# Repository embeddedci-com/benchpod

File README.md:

# BenchPod

**NOTE1: Some tagged versions will have obvious mistakes in them, but as those got built, they're in the repo for historical reasons.**

**NOTE2: Don't build these boards yourself without any necessary changes. The current tagged versions are not production-ready yet.**

**An open hardware bench tool with sensor sim, CAN, analog I/O, and power control, with a Python SDK and pytest integration.**

Embedded teams often end up with a bench full of equipment that's hard to share, hard to automate, and difficult to use remotely. Setting up tests often means being physically present, and that doesn't scale well across a team.

BenchPod is an attempt to make that easier. One board with sensor simulation over I2C and SPI, CAN bus, analog input and output, programmable power control, a logic analyzer, and an FPGA for fast protocol mocking, connected over WiFi so it can be shared across a team or accessed remotely. A Python SDK and pytest integration make it straightforward to go from manual bench work to automated tests without changing your setup.

This repo contains the KiCad source files for the board, plus the SPICE simulations used while designing the analog front ends.

---

## What's in this repo

```
pcb/
  benchpod/                      # KiCad project for the analog + digital board
    vbench-pod.kicad_pro         #   KiCad project file
    vbench-pod.kicad_pcb         #   PCB layout
    vbench-pod.kicad_sch         #   Top-level schematic
    analog-power-v2.kicad_sch    #   Analog supply rails
    analog-switching.kicad_sch   #   Analog signal routing / muxing
    analog-to-digital-v2.kicad_sch  # ADC front end
    digital-to-analog-v2.kicad_sch  # DAC output stage
    LogicAnalyzer.kicad_sch      #   Logic analyzer
    power.kicad_sch              #   Power control
    ethernet.kicad_sch           #   Ethernet
    usb.kicad_sch                #   USB
    fp-lib-table                 #   Footprint library references
    sym-lib-table                #   Symbol library references
  benchpod-digital/              # KiCad project for the digital-only board (same sheet layout)
  libs/                          # Shared symbol, footprint, and 3D-model libraries

spice/                           # LTspice / ngspice simulations for the analog front ends
  adc-v1/  adc-v2/  dac-v2/
```

Library paths in `fp-lib-table`, `sym-lib-table`, and the PCB are stored relative to
the project (`${KIPRJMOD}/..`), so the project opens in KiCad straight after cloning.

---

## Which board do I have?

The board name is printed on the silkscreen (for example "BenchPod v3-r1"). Find it in the table
below to get the git tag with the exact design files for your board:

| Silkscreen | Board | Tag | KiCad project | What changed |
|---|---|---|---|---|
| BenchPod v3 | Analog + digital | `analog-v3` | `pcb/benchpod` | First v3 board. STM32H563ZIT6, INA238 current monitors. |
| BenchPod v3-Digital | Digital only | `digital-v3` | `pcb/benchpod-digital` | First digital-only board: the v3 without the analog section. STM32H563ZGT6 (1 MB flash), INA226 current monitors. |
| BenchPod v3-r1 | Analog + digital | `analog-v3r1` | `pcb/benchpod` | STM32H563ZGT6 and INA226 like the digital board. Monitors the pod's own current (INA226 at 0x41). The 5.5 V analog rail comes from a 7 V boost instead of the 14 V rail, so U50 no longer runs hot. TPS65131 compensation caps fixed. THS4551 and TPS7A2050 in their smaller packages (RUN, DQN). |
| BenchPod v3r2-Digital | Digital only | `digital-v3r2` | `pcb/benchpod-digital` | Monitors the pod's own current (INA226 at 0x41). |
| BenchPod v3-r2 | Analog + digital | `analog-v3r2` | `pcb/benchpod` | One DAC8554 quad DAC (a channel per output) replaces the DAC8551 and its two TMUX1104 muxes. The ±14 V supply starts off and the firmware switches it on. 0.1 % resistors around the ADC driver for a smaller zero offset between pods. Fixed 9.1 pF ADC compensation instead of the trimmer. SWD and USART2 on DNP 2x2 headers instead of H1-H3. More ESD clamps (USB CC, +1V8, LA_VCCIO, the 0-5 V SMA). Board revision strap 2.70 V. |
| BenchPod v3r3-Digital | Digital only | `digital-v3r3` | `pcb/benchpod-digital` | 24-pin FFC connector (CN1) for the analog module. The module 5 V and the USB-A bridge 5 V are switched by SY6280AAC power switches, with TVS diodes on the 5 V outputs. 3.3 V buck becomes a TPS62130A with a 2.2 uH inductor. PSRAM in SOP-8. Ethernet EMI changes from the Microchip and TI reference designs: RJ45 chassis ground straight to GND, center taps fed through a 0 ohm resistor, 8.2 pF on the four data lines, a flow-through TPD4E05U06 ESD clamp. 100 nF + 470 pF at the J4, J5 and J6 terminals. Connectors placed for the enclosure. |
| BenchPod v3-r3-analog | Analog module | `analog-v3r3` | `pcb/benchpod-analog` | First analog module: the analog section on its own board, connected to the v3r3 digital board by a 24-pin FFC (CN1). Front-panel connectors for the enclosure: a lead-free BNC for the ADC input (ready for 10x probes), pluggable terminal blocks for the DAC outputs (one 6-pin block) and the 4-20 mA loop. Module ID EEPROM. +3V3 from an AP2112K-3.3. |
| BenchPod v3-r4-analog | Analog module | `analog-v3r4` | `pcb/benchpod-analog` | ADC low range: relay K5 switches the input divider from ±32.8 V to ±5.46 V for 6x the resolution. |
| BenchPod v4-Digital | Digital only | not tagged yet (on `main`) | `pcb/benchpod-digital` | First board with built-in 5 V I/O: an LSF0108 level shifter on every LA channel, 1.8, 3.3 or 5 V, J1 pin 21 as the switched and measured reference. Pull-up or pull-down with 10k, 2.2k or both on every channel (two TCA6416A). Switched DUT supplies on J1: pin 17 3.3 V behind a current-limited switch (SY6280AAC, about 1.45 A), pin 18 1.8 V from its own regulator (AP2112K-1.8). USB-A host port for the DUT's own USB (flashing and USB host). Second board revision strap. Memory-mapped W25Q. Not built yet. |
| BenchPod v4-Analog | Analog module | not tagged yet (on `main`) | `pcb/benchpod-analog` | 4-20 mA input behind a 30 mA limiter with a 100 ohm sense resistor. DAC clock and data swapped on the flat cable (pairs with the v4 digital board). More ESD clamps. Module EEPROM revision 4.0. Not built yet. |

To get the files for your board, check out its tag:

```
git checkout analog-v3r1
```

Every tag holds all KiCad projects; use the folder from the table. Older boards: `v1.0.0` and
`v1.0.1` are v1, `v2.0.0` is v2.

The v3 tags used to be named `v3.0.0` (now `analog-v3`), `v3.0.1-digital` (now `digital-v3`),
`v3.0.1-analog` (now `analog-v3r1`) and `v3.0.2-digital` (now `digital-v3r2`).

v4 is the first board with 5 V I/O. It was called digital v3r4 and analog module v3r5 while it
was designed; the feature jump made it a major version. A v4 digital board needs a v4 analog
module (or both older): the DAC lines on the flat cable are swapped.

One firmware runs on all v3 and v4 boards. The pod's own current needs firmware newer than 3.5.1.
The v3-r2 board needs firmware newer than 3.9.4: older firmware runs it as a v3-r1 and its DAC
outputs and ±12 V stay off.

---

## License

Hardware (schematics, PCB layout) is released under [CERN OHL-W v2](https://ohwr.org/cern_ohl_w_v2.txt).

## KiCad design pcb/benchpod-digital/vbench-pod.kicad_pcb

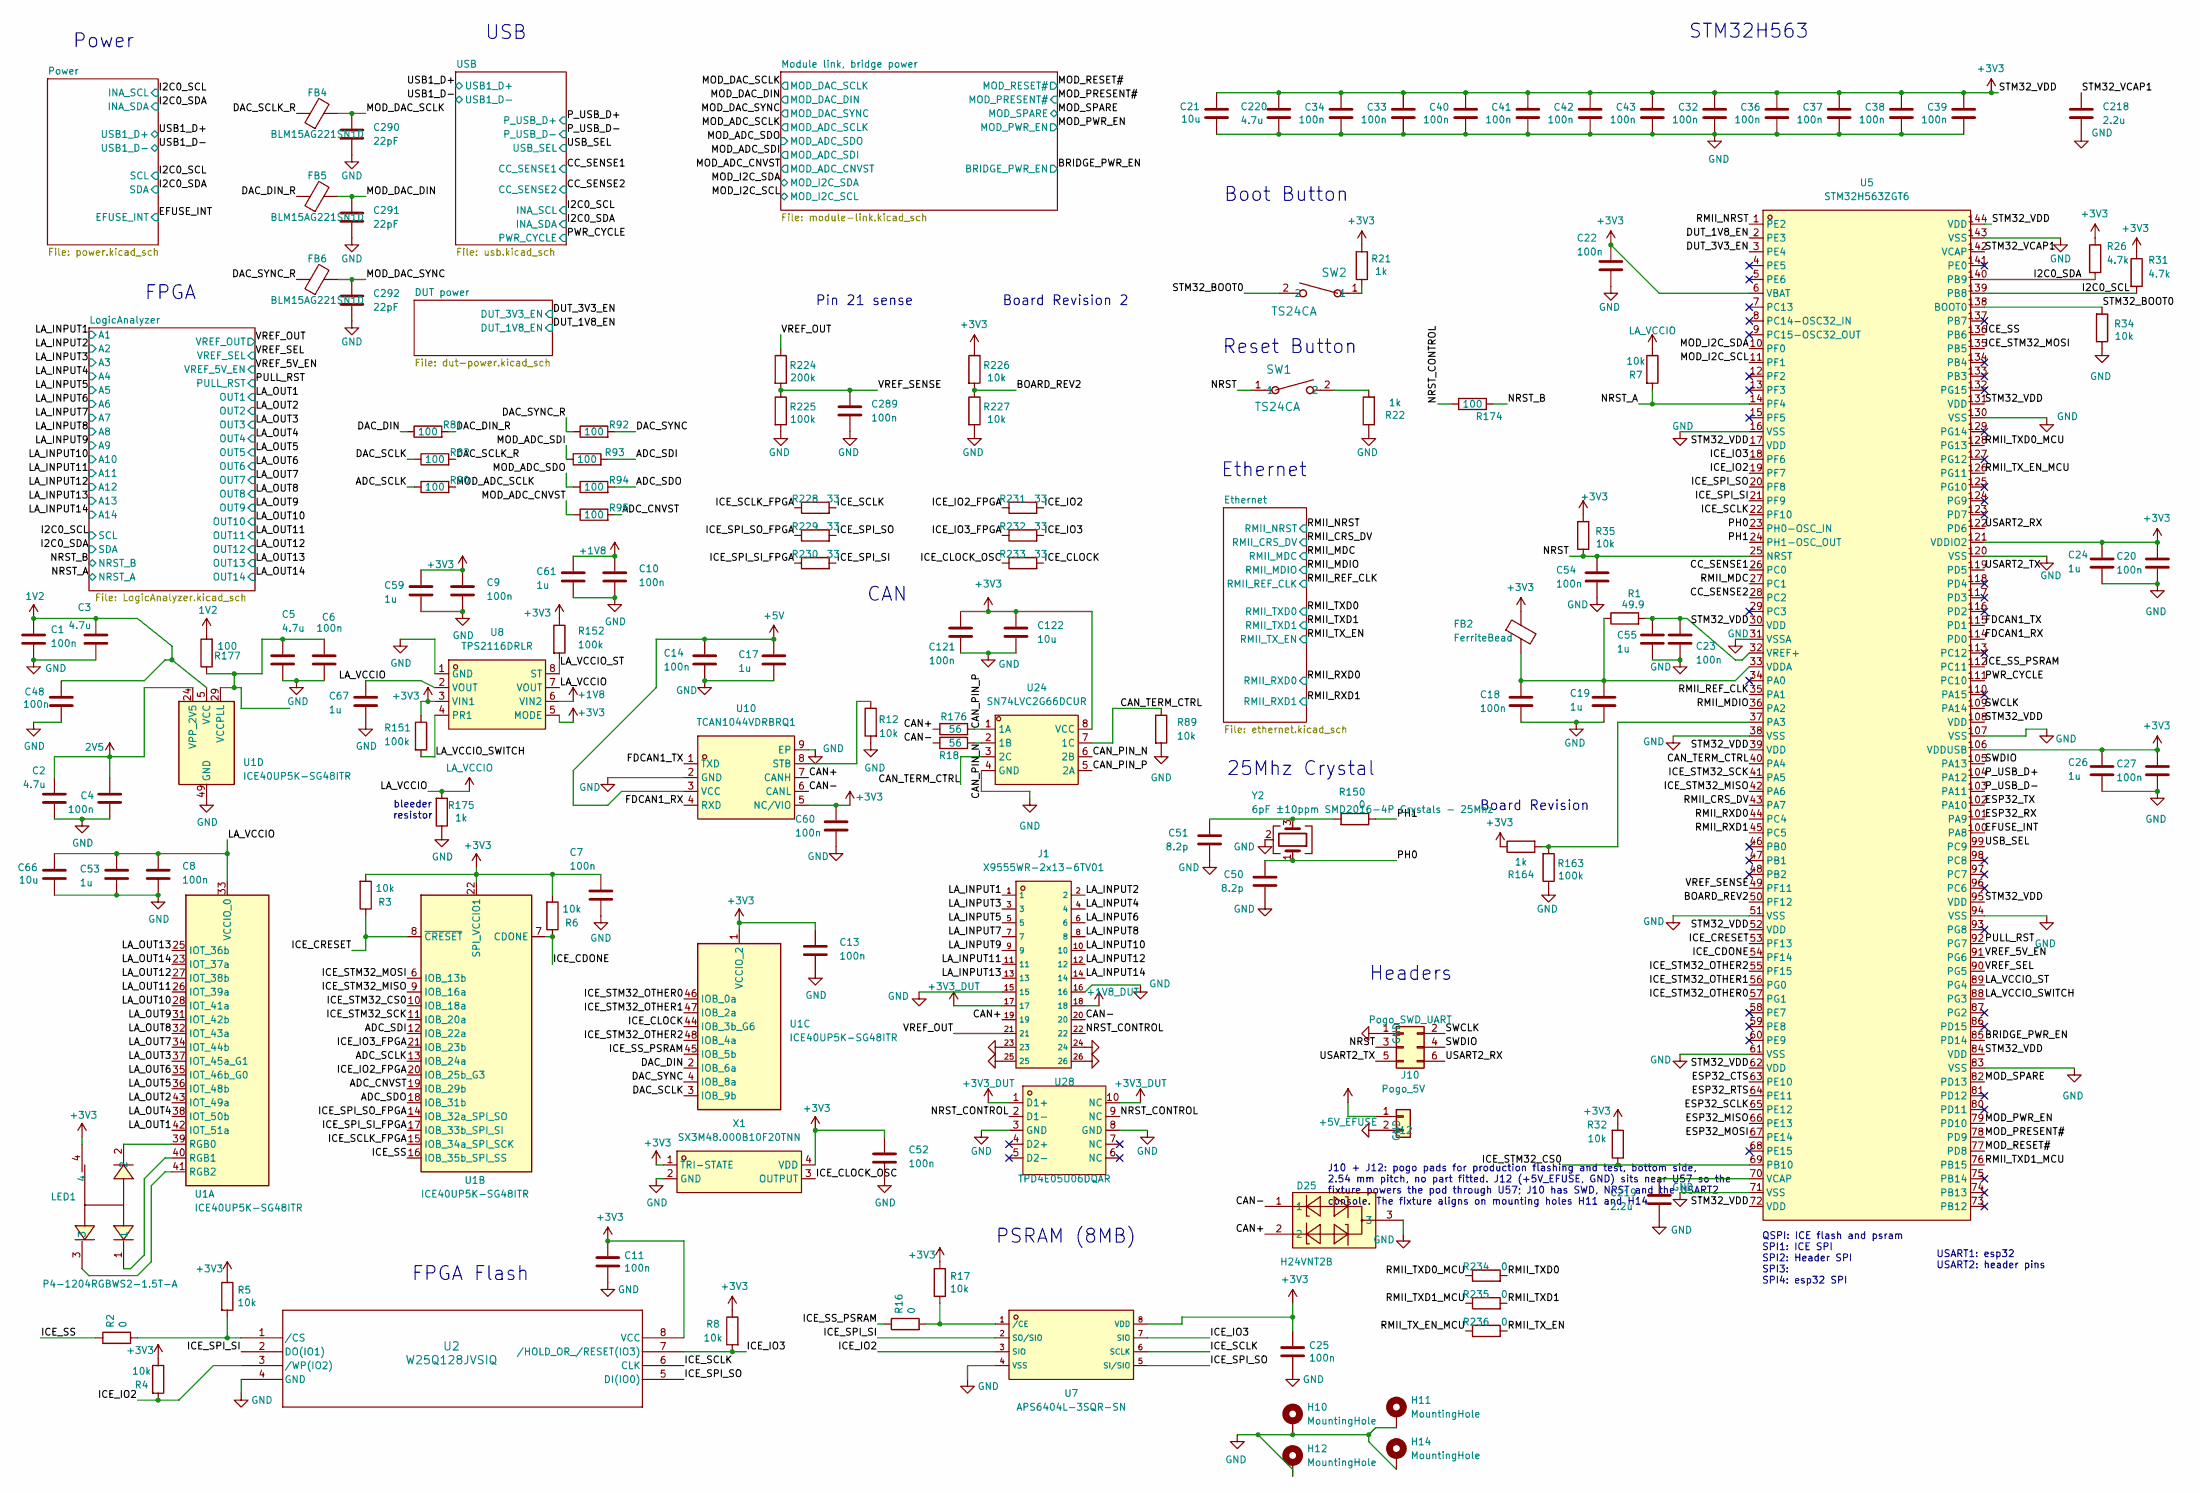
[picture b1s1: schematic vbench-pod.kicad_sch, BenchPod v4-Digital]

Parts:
C1, C4, C6, C7, C8, C9, C10, C13, C14, C18, C20, C22, C23, C27, C48, C52, C54, C60: 100n; C_0402_1005Metric; MPN CC0603KRX7R9BB104; LCSC C307331
C2, C3, C5, C220: 4.7u; C_0805_2012Metric; LCSC C98192
C11, C25, C32, C33, C34, C36, C37, C38, C39, C40, C41, C42, C43, C121, C289: 100n; C_0402_1005Metric; LCSC C307331
C17, C24, C26, C53, C59, C67: 1u; C_0402_1005Metric; MPN CL05A105KA5NQNC; LCSC C52923
C19, C55, C61: 1u; C_0402_1005Metric; MPN GRM155R61H105KE05D; LCSC C1518208
C21, C66, C122: 10u; C_0603_1608Metric; LCSC C96446
C50, C51: 8.2p; C_0402_1005Metric; LCSC C1579
C218, C219: 2.2u; C_0603_1608Metric; LCSC C415535
C290, C291, C292: 22pF; C_0402_1005Metric; MPN 0402CG220J500NT; LCSC C1555
D25: H24VNT2B; SOT-23; MPN H24VNT2B; LCSC Part C20615827
FB2: FerriteBead; C85833_L0603; LCSC C85833
FB4, FB5, FB6: BLM15AG221SN1D; L_0402_1005Metric; MPN BLM15AG221SN1D; LCSC C85813
H10, H11, H12, H14: MountingHole; MountingHole_2.7mm_M2.5_Pad_Via
J1: X9555WR-2x13-6TV01; C2682221_CONN-TH_X9555WR-2X13-6TV01; LCSC C2682221
J10: Pogo_SWD_UART; Pogo_Pads_2x03_P2.54mm
J12: Pogo_5V; Pogo_Pads_1x02_P2.54mm
LED1: P4-1204RGBWS2-1.5T-A; C2827295_LED-SMD_4P-L3.2-W1.5_P4-1204RGBWS2-1.5T-A; MPN P4-1204RGBWS2-1.5T-A; LCSC Part C2827295
R1: 49.9; R_0402_1005Metric; LCSC C325388
R2, R16, R150, R234, R235, R236: 0; R_0402_1005Metric; LCSC C17168
R3, R4, R6, R7, R8, R12, R32, R34, R35, R89, R226, R227: 10k; R_0402_1005Metric; LCSC C25744
R5, R17: 10k; R_0402_1005Metric; JLC_DNF true
R18, R176: 56; R_0402_1005Metric; LCSC C3013179
R21, R22, R164, R175: 1k; R_0402_1005Metric; LCSC C11702
R26, R31: 4.7k; R_0402_1005Metric; LCSC C25900
R81, R82, R90, R92, R93, R94, R95, R177: 100; R_0402_1005Metric; LCSC C25076
R151, R152, R163, R225: 100k; R_0402_1005Metric; LCSC C25741
R174: 100; R_0603_1608Metric; Manufacturer_Part_Number PS03W4F1000T5E; LCSC C2784878
R224: 200k; R_0402_1005Metric; LCSC C25764
R228, R229, R230, R231, R232, R233: 33; R_0402_1005Metric; LCSC C25105
SW1, SW2: TS24CA; C393942_SW-SMD_2P-TS24CA; LCSC C393942
U1: ICE40UP5K-SG48ITR; QFN-48_L7.0-W7.0-P0.50-TL-EP5.4-1; LCSC C2678152
U2: W25Q128JVSIQ; SOIC-8_L5.3-W5.3-P1.27-LS8.0-BL; MPN W25Q128JVSIQ; LCSC C97521
U5: STM32H563ZGT6; LQFP-144_L20.0-W20.0-P0.50-LS22.0-TL; LCSC Part C29271104
U7: APS6404L-3SQR-SN; C5333729_SOIC-8_L4.9-W3.9-P1.27-LS6.0-BL; LCSC C5333729
U8: TPS2116DRLR; SOT-583-8_L2.1-W1.6-P0.50-LS1.6-BL; MPN TPS2116DRLR; LCSC Part C3235557
U10: TCAN1044VDRBRQ1; VSON-8_L3.0-W3.0-P0.65-BR-EP; MPN TCAN1044VDRBRQ1; LCSC Part C5215851
U24: SN74LVC2G66DCUR; VSSOP-8_L2.1-W2.4-P0.50-LS3.2-BR; MPN SN74LVC2G66DCUR; LCSC Part C181970
U28: TPD4E05U06DQAR; C138714_USON-10_L2.5-W1.0-P0.50-BL; LCSC C138714
X1: SX3M48.000B10F20TNN; OSC-SMD_4P-L3.2-W2.5-BL; MPN SX3M48.000B10F20TNN; LCSC Part C5452690
Y2: 6pF ±10ppm SMD2016-4P Crystals - 25Mhz; Crystal_SMD_2016-4Pin_2.0x1.6mm; LCSC C49867546

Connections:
1V2: C1.2, C3.1, C48.2, R177.2, U1.5 (VCC), U1.30 (VCC); also elsewhere on the board
2V5: C2.1, C4.2, U1.24 (VPP_2V5); also elsewhere on the board
+1V8: C10.2, C61.2, U8.6 (VIN2); also elsewhere on the board
+3V3: C7.2, C9.2, C11.1, C13.2, C20.2, C21.1, C22.2, C24.2, C25.1, C26.2, C27.2, C32.1, C33.1, C34.1, C36.1, C37.1, C38.1, C39.1, C40.1, C41.1, C42.1, C43.1, C52.2, C59.2, C60.2, C121.1, C122.2, C220.1, FB2.1, LED1.4, R3.2, R4.1, R5.1, R6.2, R8.1, R17.1, R21.2, R26.1, R31.1, R32.2, R35.2, R151.1, R152.1, R164.1, R226.1, U1.1 (VCCIO_2), U1.22 (SPI_VCCIO1), U2.8 (VCC), U5.6 (VBAT), U5.17 (VDD), U5.30 (VDD), U5.39 (VDD), U5.52 (VDD), U5.62 (VDD), U5.72 (VDD), U5.84 (VDD), U5.95 (VDD), U5.106 (VDDUSB), U5.108 (VDD), U5.121 (VDDIO2), U5.131 (VDD), U5.144 (VDD), U7.8 (VDD), U8.3 (VIN1), U8.5 (MODE), U10.5 (NC/VIO), U24.8 (VCC), X1.1 (TRI-STATE), X1.4 (VDD); also elsewhere on the board
+5V: C14.2, C17.2, U10.3 (VCC); also elsewhere on the board
+5V_EFUSE: J12.1; also elsewhere on the board
/ADC_CNVST: R95.2, U1.19 (IOB_29b)
/ADC_SCLK: R90.1, U1.13 (IOB_24a)
/ADC_SDI: R93.2, U1.12 (IOB_22a)
/ADC_SDO: R94.2, U1.18 (IOB_31b)
/BOARD_REV2: R226.2, R227.1, U5.50 (PF12)
/BRIDGE_PWR_EN: U5.85 (PD14); also elsewhere on the board
/CAN+: D25.2, J1.19, R176.1, U10.7 (CANH)
/CAN-: D25.1, J1.20, R18.1, U10.6 (CANL)
/CAN_PIN_N: R18.2, U24.2 (1B), U24.6 (2B)
/CAN_PIN_P: R176.2, U24.1 (1A), U24.5 (2A)
/CAN_TERM_CTRL: R89.1, U5.40 (PA4), U24.3 (2C), U24.7 (1C)
/CC_SENSE1: U5.26 (PC0); also elsewhere on the board
/CC_SENSE2: U5.28 (PC2); also elsewhere on the board
/DAC_DIN: R81.1, U1.2 (IOB_6a)
/DAC_DIN_R: FB5.1, R81.2
/DAC_SCLK: R82.1, U1.3 (IOB_9b)
/DAC_SCLK_R: FB4.1, R82.2
/DAC_SYNC: R92.2, U1.4 (IOB_8a)
/DAC_SYNC_R: FB6.1, R92.1
/DUT_1V8_EN: U5.2 (PE3); also elsewhere on the board
/DUT_3V3_EN: U5.3 (PE4); also elsewhere on the board
/EFUSE_INT: U5.100 (PA8); also elsewhere on the board
/ESP32_CTS: U5.63 (PE10)
/ESP32_MISO: U5.66 (PE13)
/ESP32_MOSI: U5.67 (PE14)
/ESP32_RTS: U5.64 (PE11)
/ESP32_RX: U5.101 (PA9)
/ESP32_SCLK: U5.65 (PE12)
/ESP32_TX: U5.102 (PA10)
/FDCAN1_RX: U5.114 (PD0), U10.4 (RXD)
/FDCAN1_TX: U5.115 (PD1), U10.1 (TXD)
/I2C0_SCL: R31.2, U5.139 (PB8); also elsewhere on the board
/I2C0_SDA: R26.2, U5.140 (PB9); also elsewhere on the board
/ICE_CDONE: R6.1, U1.7 (CDONE), U5.54 (PF14)
/ICE_CLOCK: R233.2, U1.44 (IOB_3b_G6)
/ICE_CLOCK_OSC: R233.1, X1.3 (OUTPUT)
/ICE_CRESET: R3.1, U1.8 (~CRESET), U5.53 (PF13)
/ICE_IO2: R4.2, R231.2, U2.3 (/WP(IO2)), U5.19 (PF7), U7.3 (SIO)
/ICE_IO2_FPGA: R231.1, U1.20 (IOB_25b_G3)
/ICE_IO3: R8.2, R232.2, U2.7 (/HOLD_OR_/RESET(IO3)), U5.18 (PF6), U7.7 (SIO)
/ICE_IO3_FPGA: R232.1, U1.21 (IOB_23b)
/ICE_SCLK: R228.2, U2.6 (CLK), U5.22 (PF10), U7.6 (SCLK)
/ICE_SCLK_FPGA: R228.1, U1.15 (IOB_34a_SPI_SCK)
/ICE_SPI_SI: R230.2, U2.2 (DO(IO1)), U5.21 (PF9), U7.2 (SO/SIO)
/ICE_SPI_SI_FPGA: R230.1, U1.17 (IOB_33b_SPI_SI)
/ICE_SPI_SO: R229.2, U2.5 (DI(IO0)), U5.20 (PF8), U7.5 (SI/SIO)
/ICE_SPI_SO_FPGA: R229.1, U1.14 (IOB_32a_SPI_SO)
/ICE_SS: R2.1, U1.16 (IOB_35b_SPI_SS), U5.136 (PB6)
/ICE_SS_PSRAM: R16.1, U1.45 (IOB_5b), U5.112 (PC11)
/ICE_STM32_CS0: R32.1, U1.10 (IOB_18a), U5.69 (PB10)
/ICE_STM32_MISO: U1.9 (IOB_16a), U5.42 (PA6)
/ICE_STM32_MOSI: U1.6 (IOB_13b), U5.135 (PB5)
/ICE_STM32_OTHER0: U1.46 (IOB_0a), U5.57 (PG1)
/ICE_STM32_OTHER1: U1.47 (IOB_2a), U5.56 (PG0)
/ICE_STM32_OTHER2: U1.48 (IOB_4a), U5.55 (PF15)
/ICE_STM32_SCK: U1.11 (IOB_20a), U5.41 (PA5)
/LA_INPUT1: J1.1; also elsewhere on the board
/LA_INPUT2: J1.2; also elsewhere on the board
/LA_INPUT3: J1.3; also elsewhere on the board
/LA_INPUT4: J1.4; also elsewhere on the board
/LA_INPUT5: J1.5; also elsewhere on the board
/LA_INPUT6: J1.6; also elsewhere on the board
/LA_INPUT7: J1.7; also elsewhere on the board
/LA_INPUT8: J1.8; also elsewhere on the board
/LA_INPUT9: J1.9; also elsewhere on the board
/LA_INPUT10: J1.10; also elsewhere on the board
/LA_INPUT11: J1.11; also elsewhere on the board
/LA_INPUT12: J1.12; also elsewhere on the board
/LA_INPUT13: J1.13; also elsewhere on the board
/LA_INPUT14: J1.14; also elsewhere on the board
/LA_OUT1: U1.42 (IOT_51a); also elsewhere on the board
/LA_OUT2: U1.43 (IOT_49a); also elsewhere on the board
/LA_OUT3: U1.37 (IOT_45a_G1); also elsewhere on the board
/LA_OUT4: U1.38 (IOT_50b); also elsewhere on the board
/LA_OUT5: U1.36 (IOT_48b); also elsewhere on the board
/LA_OUT6: U1.35 (IOT_46b_G0); also elsewhere on the board
/LA_OUT7: U1.34 (IOT_44b); also elsewhere on the board
/LA_OUT8: U1.32 (IOT_43a); also elsewhere on the board
/LA_OUT9: U1.31 (IOT_42b); also elsewhere on the board
/LA_OUT10: U1.28 (IOT_41a); also elsewhere on the board
/LA_OUT11: U1.26 (IOT_39a); also elsewhere on the board
/LA_OUT12: U1.27 (IOT_38b); also elsewhere on the board
/LA_OUT13: U1.25 (IOT_36b); also elsewhere on the board
/LA_OUT14: U1.23 (IOT_37a); also elsewhere on the board
/LA_VCCIO_ST: R152.2, U5.89 (PG4), U8.8 (ST)
/LA_VCCIO_SWITCH: R151.2, U5.88 (PG3), U8.4 (PR1)
/MOD_ADC_CNVST: R95.1; also elsewhere on the board
/MOD_ADC_SCLK: R90.2; also elsewhere on the board
/MOD_ADC_SDI: R93.1; also elsewhere on the board
/MOD_ADC_SDO: R94.1; also elsewhere on the board
/MOD_DAC_DIN: C291.1, FB5.2; also elsewhere on the board
/MOD_DAC_SCLK: C290.1, FB4.2; also elsewhere on the board
/MOD_DAC_SYNC: C292.1, FB6.2; also elsewhere on the board
/MOD_I2C_SCL: U5.11 (PF1); also elsewhere on the board
/MOD_I2C_SDA: U5.10 (PF0); also elsewhere on the board
/MOD_PRESENT#: U5.78 (PD9); also elsewhere on the board
/MOD_PWR_EN: U5.79 (PD10); also elsewhere on the board
/MOD_RESET#: U5.77 (PD8); also elsewhere on the board
/MOD_SPARE: U5.82 (PD13); also elsewhere on the board
/NRST: C54.2, J10.3, R35.1, SW1.1, U5.25 (NRST)
/NRST_A: R7.2, U5.14 (PF4); also elsewhere on the board
/NRST_B: R174.2; also elsewhere on the board
/NRST_CONTROL: J1.22, R174.1, U28.2 (D1-), U28.9 (NC)
/PH0: C50.1, U5.23 (PH0-OSC_IN), Y2.1
/PH1: R150.1, U5.24 (PH1-OSC_OUT)
/PULL_RST: U5.92 (PG7); also elsewhere on the board
/PWR_CYCLE: U5.111 (PC10); also elsewhere on the board
/P_USB_D+: U5.104 (PA12); also elsewhere on the board
/P_USB_D-: U5.103 (PA11); also elsewhere on the board
/RMII_CRS_DV: U5.43 (PA7); also elsewhere on the board
/RMII_MDC: U5.27 (PC1); also elsewhere on the board
/RMII_MDIO: U5.36 (PA2); also elsewhere on the board
/RMII_NRST: U5.1 (PE2); also elsewhere on the board
/RMII_REF_CLK: U5.35 (PA1); also elsewhere on the board
/RMII_RXD0: U5.44 (PC4); also elsewhere on the board
/RMII_RXD1: U5.45 (PC5); also elsewhere on the board
/RMII_TXD0: R234.2; also elsewhere on the board
/RMII_TXD0_MCU: R234.1, U5.128 (PG13)
/RMII_TXD1: R235.2; also elsewhere on the board
/RMII_TXD1_MCU: R235.1, U5.76 (PB15)
/RMII_TX_EN: R236.2; also elsewhere on the board
/RMII_TX_EN_MCU: R236.1, U5.126 (PG11)
/STM32_BOOT0: R34.2, SW2.2, U5.138 (BOOT0)
/STM32_VCAP1: C218.1, U5.142 (VCAP)
/SWCLK: J10.2, U5.109 (PA14)
/SWDIO: J10.4, U5.105 (PA13)
/USART2_RX: J10.6, U5.122 (PD6)
/USART2_TX: J10.5, U5.119 (PD5)
/USB_SEL: U5.99 (PC9); also elsewhere on the board
/VREF_5V_EN: U5.91 (PG6); also elsewhere on the board
/VREF_OUT: J1.21, R224.1; also elsewhere on the board
/VREF_SEL: U5.90 (PG5); also elsewhere on the board
/VREF_SENSE: C289.1, R224.2, R225.1, U5.49 (PF11)
GND: C1.1, C2.2, C3.2, C4.1, C5.1, C6.1, C7.1, C8.1, C9.1, C10.1, C11.2, C13.1, C14.1, C17.1, C18.1, C19.1, C20.1, C21.2, C22.1, C23.1, C24.1, C25.2, C26.1, C27.1, C32.2, C33.2, C34.2, C36.2, C37.2, C38.2, C39.2, C40.2, C41.2, C42.2, C43.2, C48.1, C50.2, C51.2, C52.1, C53.1, C54.1, C55.1, C59.1, C60.1, C61.1, C66.2, C67.1, C121.2, C122.1, C218.2, C219.2, C220.2, C289.2, C290.2, C291.2, C292.2, D25.3, H10.1 (1_1), H11.1 (1_1), H12.1 (1_1), H14.1 (1_1), J1.15, J1.16, J1.23, J1.24, J1.25, J1.26, J10.1, J12.2, R12.2, R22.1, R34.1, R89.2, R163.1, R175.1, R225.2, R227.2, U1.49 (GND), U2.4 (GND), U5.16 (VSS), U5.31 (VSSA), U5.38 (VSS), U5.51 (VSS), U5.61 (VSS), U5.71 (VSS), U5.83 (VSS), U5.94 (VSS), U5.107 (VSS), U5.120 (VSS), U5.130 (VSS), U5.143 (VSS), U7.4 (VSS), U8.1 (GND), U10.2 (GND), U10.9 (EP), U24.4 (GND), U28.3 (GND), U28.8 (GND), X1.2 (GND), Y2.2 (G), Y2.4 (G); also elsewhere on the board
LA_VCCIO: C8.2, C53.2, C66.1, C67.2, R7.1, R175.2, U1.33 (VCCIO_0), U8.2 (VOUT), U8.7 (VOUT); also elsewhere on the board
unnamed: C51.1, R150.2, Y2.3
unnamed: C219.1, U5.70 (VCAP)
unnamed: R21.1, SW2.1
unnamed: R22.2, SW1.2
unnamed: LED1.2, U1.39 (RGB0)
unnamed: LED1.1, U1.40 (RGB1)
unnamed: LED1.3, U1.41 (RGB2)
unnamed: C5.2, C6.2, R177.1, U1.29 (VCCPLL)
unnamed: R2.2, R5.2, U2.1 (/CS)
unnamed: R163.2, R164.2, U5.37 (PA3)
unnamed: C18.2, C19.2, FB2.2, R1.1, U5.33 (VDDA)
unnamed: C23.2, C55.2, R1.2, U5.32 (VREF+)
unnamed: R16.2, R17.2, U7.1 (/CE)
unnamed: R12.1, U10.8 (STB)

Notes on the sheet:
bleeder resistor
Pin 21 sense
CAN
QSPI: ICE flash and psram SPI1: ICE SPI SPI2: Header SPI SPI3: SPI4: esp32 SPI
STM32H563
USB
Ethernet
Board Revision 2
25Mhz Crystal
Reset Button
FPGA Flash
FPGA
Boot Button
Headers
J10 + J12: pogo pads for production flashing and test, bottom side, 2.54 mm pitch, no part fitted. J12 (+5V_EFUSE, GND) sits near U57 so the fixture powers the pod through U57; J10 has SWD, NRST and the USART2 console. The fixture aligns on mounting holes H11 and H14.
USART1: esp32 USART2: header pins
PSRAM (8MB)
Power
Board Revision

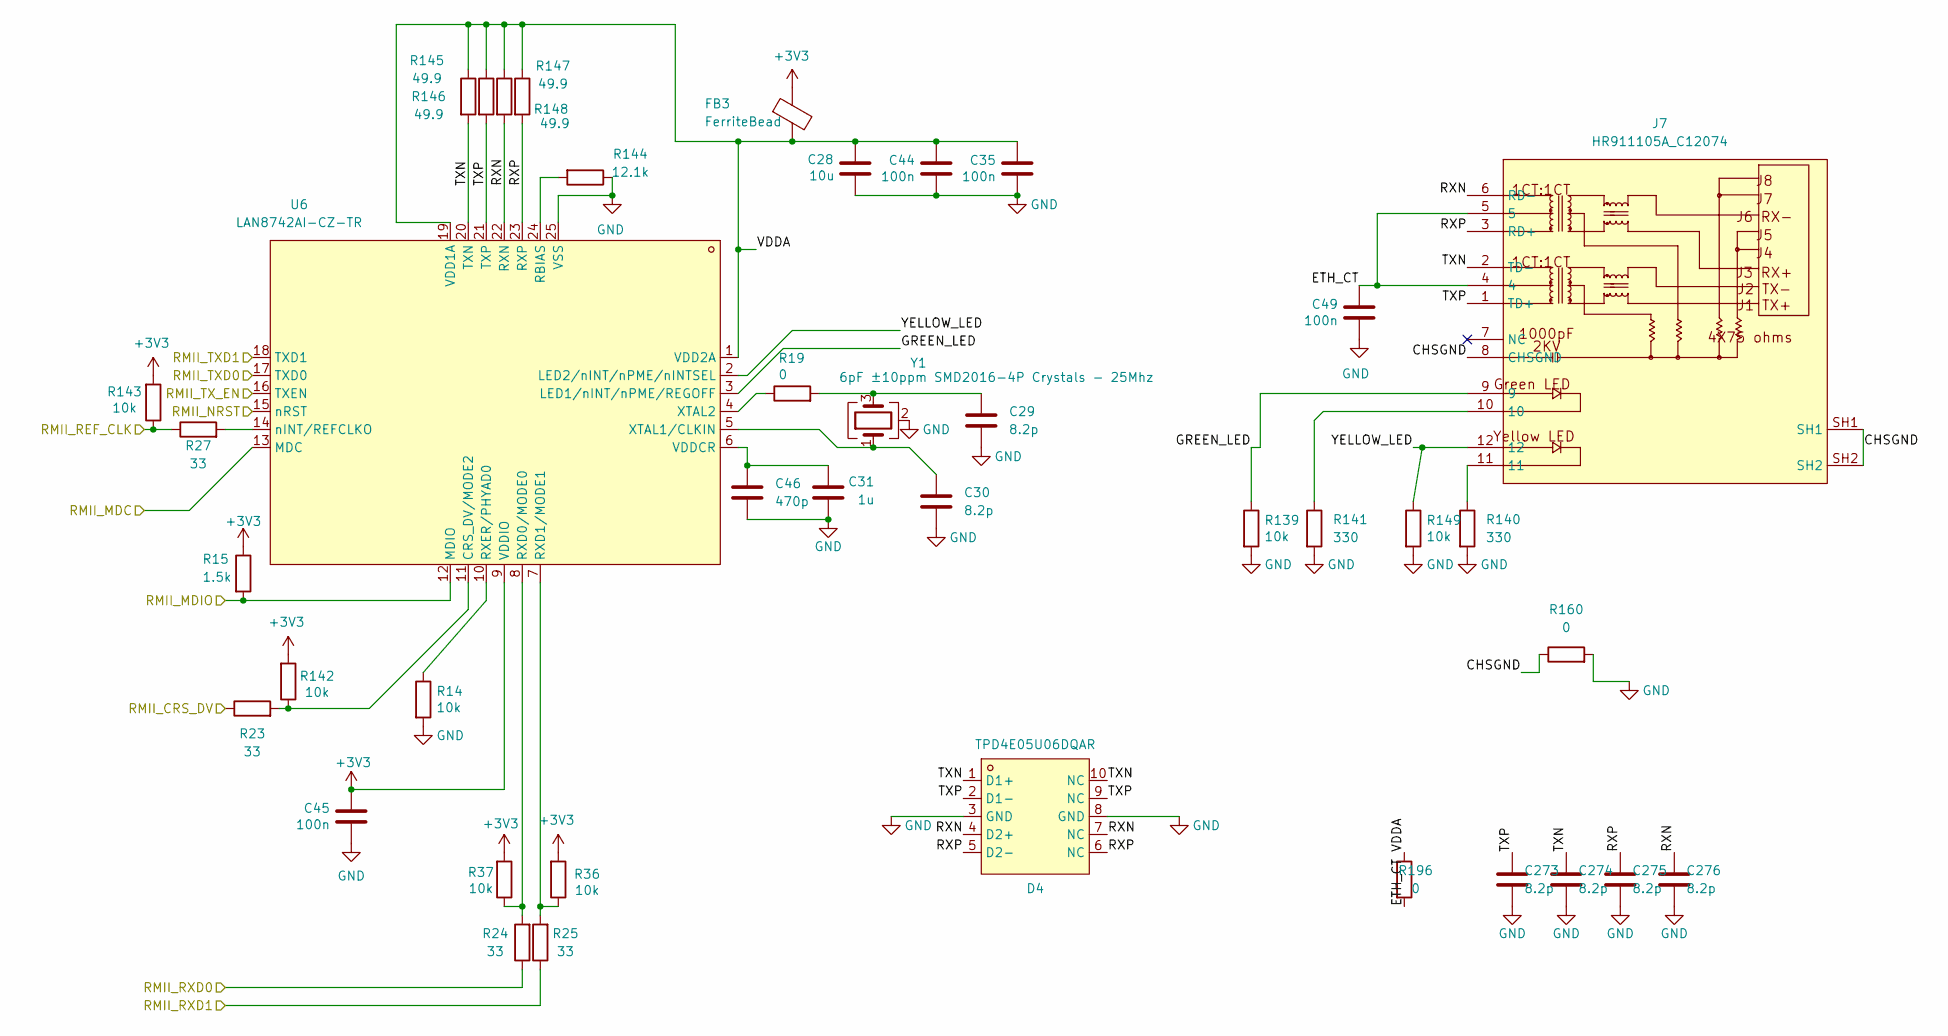
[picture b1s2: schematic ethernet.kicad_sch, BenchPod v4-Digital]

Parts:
C28: 10u; C_0603_1608Metric; LCSC C96446
C29, C30, C273, C274, C275, C276: 8.2p; C_0402_1005Metric; LCSC C1579
C31: 1u; C_0402_1005Metric; MPN GRM155R61H105KE05D; LCSC C1518208
C35, C44, C45, C49: 100n; C_0402_1005Metric; LCSC C307331
C46: 470p; C_0402_1005Metric; LCSC C1537
D4: TPD4E05U06DQAR; C138714_USON-10_L2.5-W1.0-P0.50-BL; LCSC C138714
FB3: FerriteBead; C85833_L0603; LCSC C85833
J7: HR911105A_C12074; RJ45-TH_HR911105A; MPN HR911105A; LCSC Part C12074
R14, R139, R149: 10k; R_0402_1005Metric; JLC_DNF true
R15: 1.5k; R_0402_1005Metric; LCSC C25867
R19, R160, R196: 0; R_0402_1005Metric; LCSC C17168
R23, R24, R25, R27: 33; R_0402_1005Metric; LCSC C25105
R36, R37, R142, R143: 10k; R_0402_1005Metric; LCSC C25744
R140, R141: 330; R_0402_1005Metric; LCSC C25104
R144: 12.1k; R_0402_1005Metric; LCSC C25852
R145, R146, R147, R148: 49.9; R_0402_1005Metric; LCSC C325388
U6: LAN8742AI-CZ-TR; VQFN-24_L4.0-W4.0-P0.50-BL-EP2.5; MPN LAN8742AI-CZ-TR; LCSC Part C621425
Y1: 6pF ±10ppm SMD2016-4P Crystals - 25Mhz; Crystal_SMD_2016-4Pin_2.0x1.6mm; LCSC C49867546

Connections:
+3V3: C45.1, FB3.1, R15.1, R36.2, R37.2, R142.2, R143.2, U6.9 (VDDIO); also elsewhere on the board
/Ethernet/CHSGND: J7.8 (CHSGND), J7.SH1, J7.SH2, R160.1
/Ethernet/ETH_CT: C49.1, J7.4, J7.5, R196.2
/Ethernet/GREEN_LED: J7.9, R139.1, U6.3 (LED1/nINT/nPME/REGOFF)
/Ethernet/RXN: C276.1, D4.4 (D2+), D4.7 (NC), J7.6 (RD-), R147.2, U6.22 (RXN)
/Ethernet/RXP: C275.1, D4.5 (D2-), D4.6 (NC), J7.3 (RD+), R148.2, U6.23 (RXP)
/Ethernet/TXN: C274.1, D4.1 (D1+), D4.10 (NC), J7.2 (TD-), R145.2, U6.20 (TXN)
/Ethernet/TXP: C273.1, D4.2 (D1-), D4.9 (NC), J7.1 (TD+), R146.2, U6.21 (TXP)
/Ethernet/VDDA: C28.1, C35.1, C44.1, FB3.2, R145.1, R146.1, R147.1, R148.1, R196.1, U6.1 (VDD2A), U6.19 (VDD1A)
/Ethernet/YELLOW_LED: J7.12, R149.1, U6.2 (LED2/nINT/nPME/nINTSEL)
/RMII_CRS_DV: R23.1; also elsewhere on the board
/RMII_MDC: U6.13 (MDC); also elsewhere on the board
/RMII_MDIO: R15.2, U6.12 (MDIO); also elsewhere on the board
/RMII_NRST: U6.15 (nRST); also elsewhere on the board
/RMII_REF_CLK: R27.1, R143.1; also elsewhere on the board
/RMII_RXD0: R24.1; also elsewhere on the board
/RMII_RXD1: R25.1; also elsewhere on the board
/RMII_TXD0: U6.17 (TXD0); also elsewhere on the board
/RMII_TXD1: U6.18 (TXD1); also elsewhere on the board
/RMII_TX_EN: U6.16 (TXEN); also elsewhere on the board
GND: C28.2, C29.2, C30.2, C31.1, C35.2, C44.2, C45.2, C46.2, C49.2, C273.2, C274.2, C275.2, C276.2, D4.3 (GND), D4.8 (GND), R14.2, R139.2, R140.2, R141.2, R144.1, R149.2, R160.2, U6.25 (VSS), Y1.2 (G), Y1.4 (G); also elsewhere on the board
unnamed: C29.1, R19.2, Y1.3
unnamed: J7.10, R141.1
unnamed: J7.11, R140.1
unnamed: R23.2, R142.1, U6.11 (CRS_DV/MODE2)
unnamed: R144.2, U6.24 (RBIAS)
unnamed: R24.2, R37.1, U6.8 (RXD0/MODE0)
unnamed: R25.2, R36.1, U6.7 (RXD1/MODE1)
unnamed: R14.1, U6.10 (RXER/PHYAD0)
unnamed: C31.2, C46.1, U6.6 (VDDCR)
unnamed: C30.1, U6.5 (XTAL1/CLKIN), Y1.1
unnamed: R19.1, U6.4 (XTAL2)
unnamed: R27.2, U6.14 (nINT/REFCLKO)

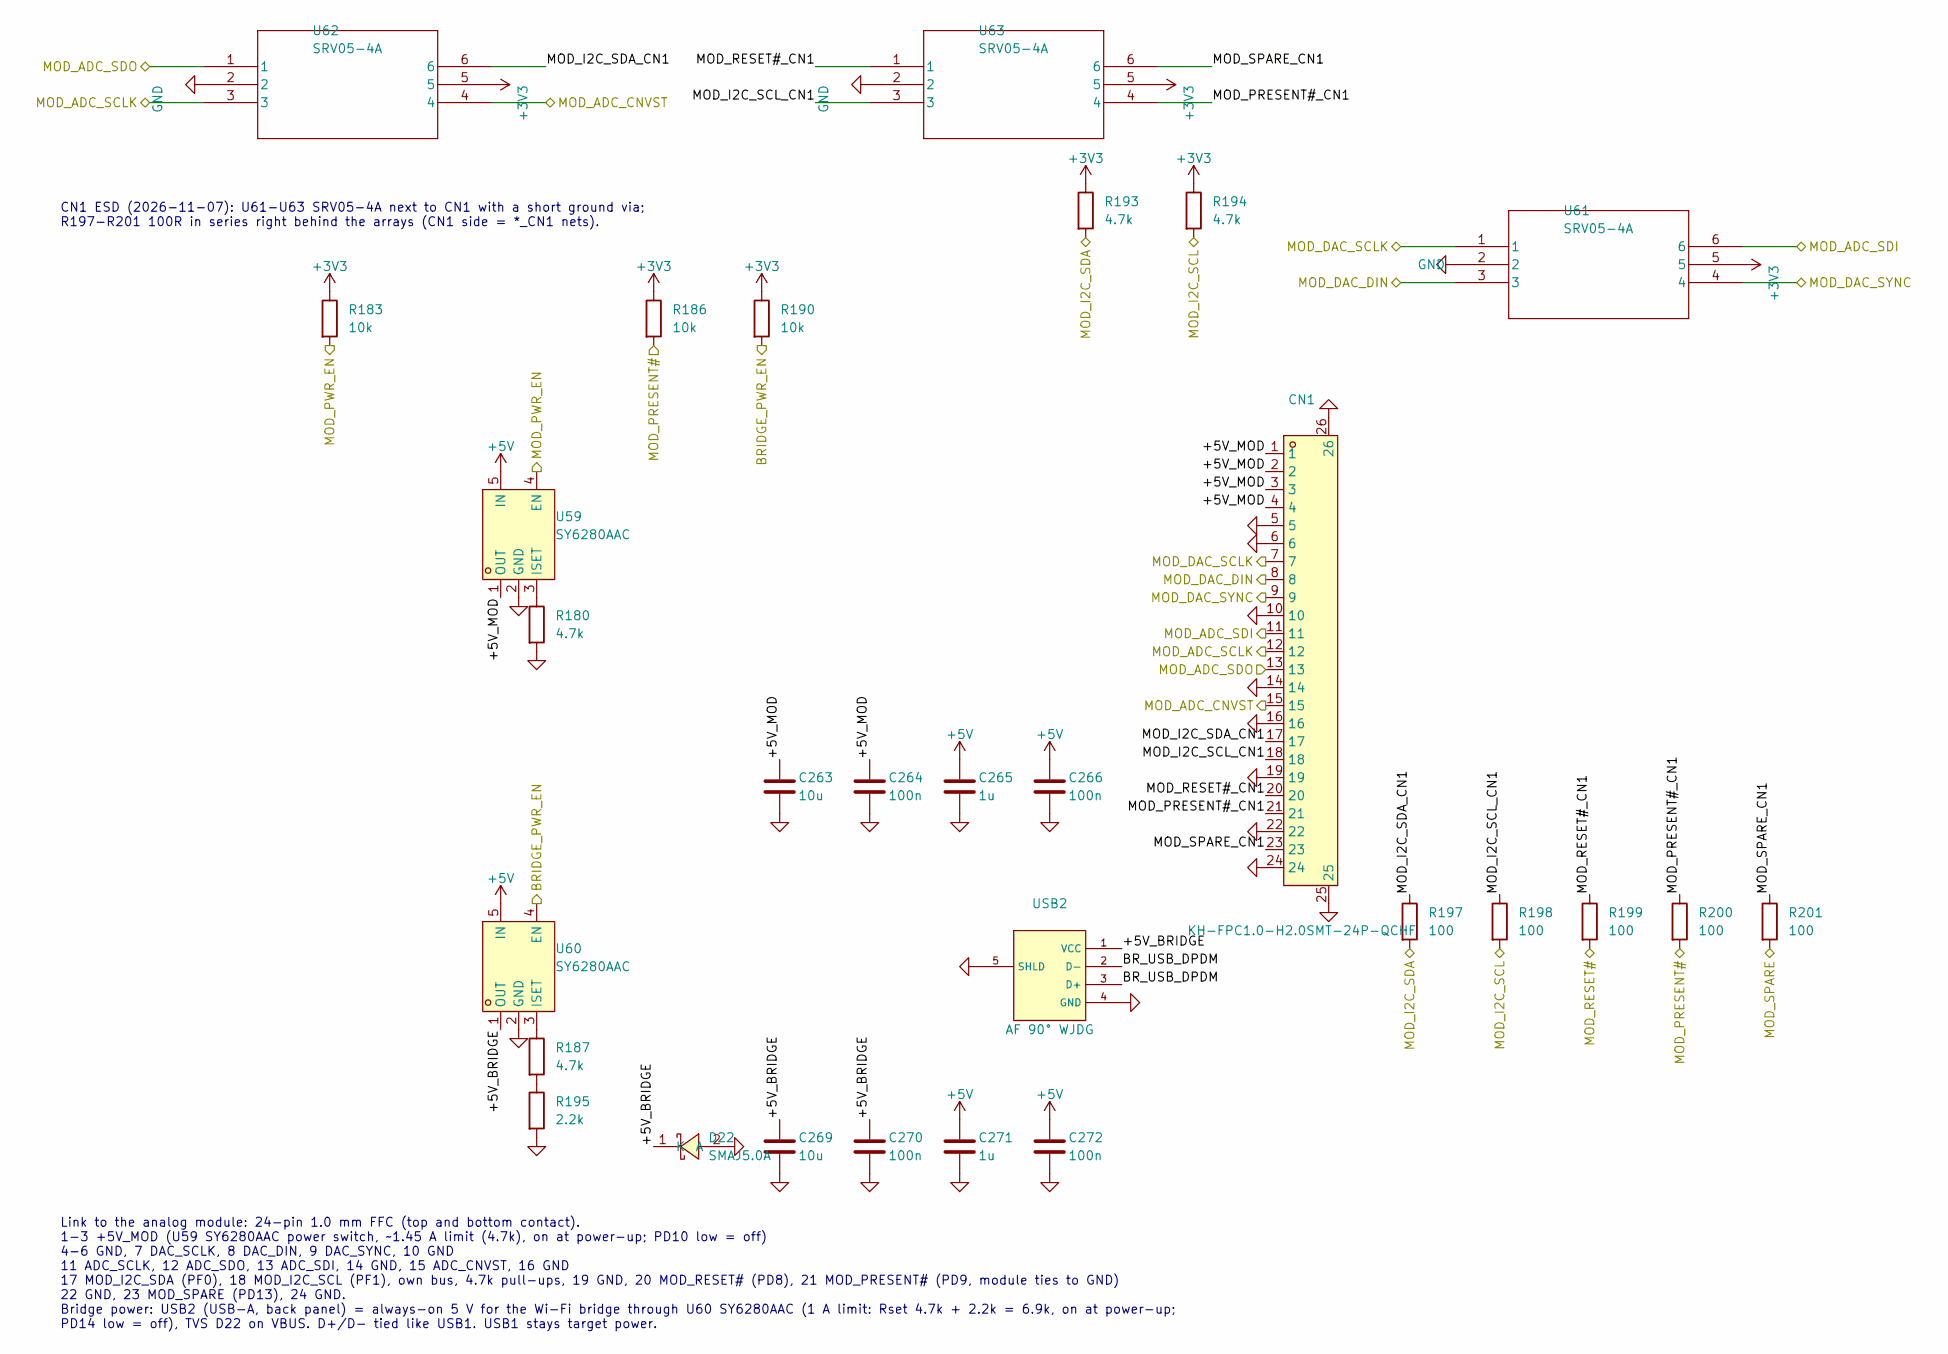
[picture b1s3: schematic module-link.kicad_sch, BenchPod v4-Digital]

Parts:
C263, C269: 10u; C_0603_1608Metric; LCSC C96446
C264, C266, C270, C272: 100n; C_0402_1005Metric; MPN CC0603KRX7R9BB104; LCSC C307331
C265, C271: 1u; C_0402_1005Metric; MPN CL05A105KA5NQNC; LCSC C52923
CN1: KH-FPC1.0-H2.0SMT-24P-QCHF; C5123103_FPC-SMD_24P-P1.00_KH-FPC1.0-H2.0SMT-24P-QCHF; LCSC C5123103
D22: SMAJ5.0A; SMA_L4.3-W2.6-LS5.0-RD; MPN SMAJ5.0A; LCSC Part C2925443
R180, R187, R193, R194: 4.7k; R_0402_1005Metric; LCSC C25900
R183, R186, R190: 10k; R_0402_1005Metric; LCSC C25744
R195: 2.2k; R_0402_1005Metric; LCSC C25879
R197, R198, R199, R200, R201: 100; R_0402_1005Metric; LCSC C25076
U59, U60: SY6280AAC; C55136_SOT-23-5_L3.0-W1.7-P0.95-LS2.8-BL; LCSC C55136
U61, U62, U63: SRV05-4A; SOT-23-6_L2.9-W1.6-P0.95-LS2.8-BR; LCSC C20615829
USB2: AF 90° WJDG; C456018_USB-A-TH_AF-WJDG; LCSC C456018

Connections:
+3V3: R183.1, R186.1, R190.1, R193.1, R194.1, U61.5, U62.5, U63.5; also elsewhere on the board
+5V: C265.1, C266.1, C271.1, C272.1, U59.5 (IN), U60.5 (IN); also elsewhere on the board
/BRIDGE_PWR_EN: R190.2, U60.4 (EN); also elsewhere on the board
/MOD_ADC_CNVST: CN1.15, U62.4; also elsewhere on the board
/MOD_ADC_SCLK: CN1.12, U62.3; also elsewhere on the board
/MOD_ADC_SDI: CN1.11, U61.6; also elsewhere on the board
/MOD_ADC_SDO: CN1.13, U62.1; also elsewhere on the board
/MOD_DAC_DIN: CN1.8, U61.3; also elsewhere on the board
/MOD_DAC_SCLK: CN1.7, U61.1; also elsewhere on the board
/MOD_DAC_SYNC: CN1.9, U61.4; also elsewhere on the board
/MOD_I2C_SCL: R194.2, R198.2; also elsewhere on the board
/MOD_I2C_SDA: R193.2, R197.2; also elsewhere on the board
/MOD_PRESENT#: R186.2, R200.2; also elsewhere on the board
/MOD_PWR_EN: R183.2, U59.4 (EN); also elsewhere on the board
/MOD_RESET#: R199.2; also elsewhere on the board
/MOD_SPARE: R201.2; also elsewhere on the board
/Module link, bridge power/+5V_BRIDGE: C269.1, C270.1, D22.1 (K), U60.1 (OUT), USB2.1 (VCC)
/Module link, bridge power/+5V_MOD: C263.1, C264.1, CN1.1, CN1.2, CN1.3, CN1.4, U59.1 (OUT)
/Module link, bridge power/BR_USB_DPDM: USB2.2 (D-), USB2.3 (D+)
/Module link, bridge power/MOD_I2C_SCL_CN1: CN1.18, R198.1, U63.3
/Module link, bridge power/MOD_I2C_SDA_CN1: CN1.17, R197.1, U62.6
/Module link, bridge power/MOD_PRESENT#_CN1: CN1.21, R200.1, U63.4
/Module link, bridge power/MOD_RESET#_CN1: CN1.20, R199.1, U63.1
/Module link, bridge power/MOD_SPARE_CN1: CN1.23, R201.1, U63.6
GND: C263.2, C264.2, C265.2, C266.2, C269.2, C270.2, C271.2, C272.2, CN1.5, CN1.6, CN1.10, CN1.14, CN1.16, CN1.19, CN1.22, CN1.24, CN1.25, CN1.26, D22.2 (A), R180.2, R195.2, U59.2 (GND), U60.2 (GND), U61.2, U62.2, U63.2, USB2.4 (GND), USB2.5 (SHLD); also elsewhere on the board
unnamed: R187.2, R195.1
unnamed: R180.1, U59.3 (ISET)
unnamed: R187.1, U60.3 (ISET)

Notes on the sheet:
Link to the analog module: 24-pin 1.0 mm FFC (top and bottom contact). 1-3 +5V_MOD (U59 SY6280AAC power switch, ~1.45 A limit (4.7k), on at power-up; PD10 low = off) 4-6 GND, 7 DAC_SCLK, 8 DAC_DIN, 9 DAC_SYNC, 10 GND 11 ADC_SCLK, 12 ADC_SDO, 13 ADC_SDI, 14 GND, 15 ADC_CNVST, 16 GND 17 MOD_I2C_SDA (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
CN1 ESD (2026-11-07): U61-U63 SRV05-4A next to CN1 with a short ground via; R197-R201 100R in series right behind the arrays (CN1 side = *_CN1 nets).
